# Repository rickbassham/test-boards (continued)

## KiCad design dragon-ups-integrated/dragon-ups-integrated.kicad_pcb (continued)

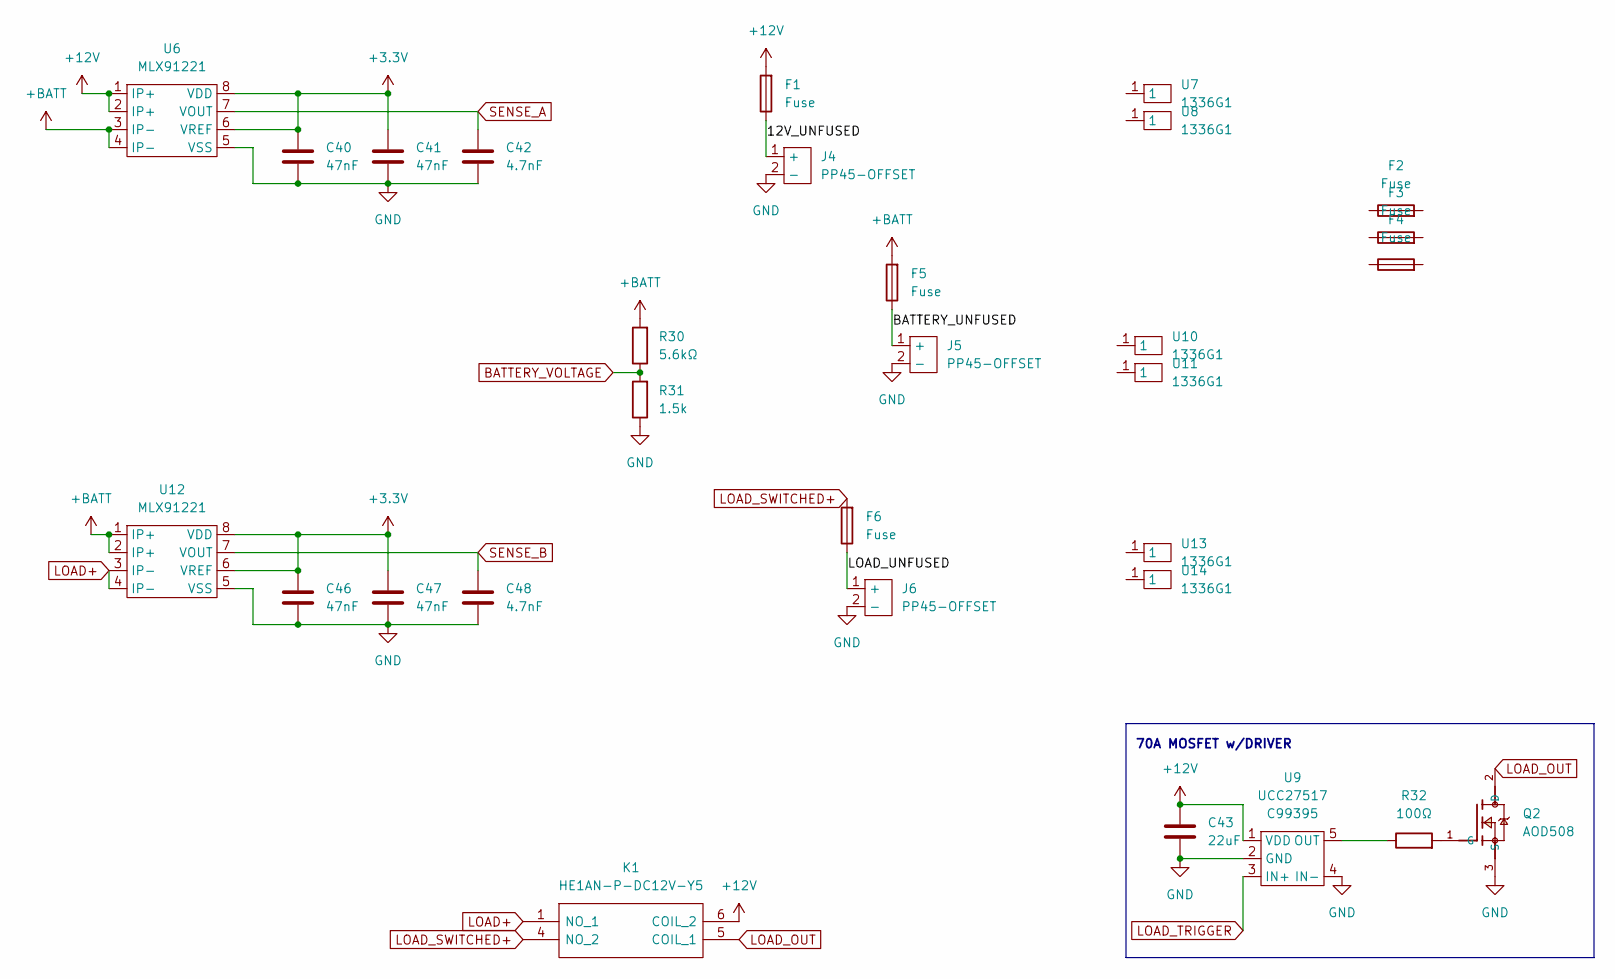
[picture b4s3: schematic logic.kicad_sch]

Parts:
C40, C41, C46, C47: 47nF; C_0603_1608Metric; LCSC C1622
C42, C48: 4.7nF; C_0603_1608Metric; LCSC C53987
C43: 22uF; C_0805_2012Metric; LCSC C45783
F1, F5, F6: Fuse; Keystone 3522-2 Fuse Holder; Manufacturer Part 3522-2; DigiKey Part 36-3522-2-ND
F2, F3, F4: Fuse; Manufacturer Part 0287030.PXCN; DigiKey Part F4202-ND
J4, J5, J6: PP45-OFFSET; PP45-SHORT; Manufacturer Part 1336G1; DigiKey Part 2243-1336G1-ND
K1: HE1AN-P-DC12V-Y5; HE1ANPDC6VY5; Manufacturer_Part_Number HE1AN-P-DC6V-Y5; Mouser Part Number 769-HE1AN-P-DC6V-Y5
Q2: AOD508; TO-252-2; LCSC C80964
R30: 5.6kΩ; R_0805_2012Metric; LCSC C4382
R31: 1.5k; R_0805_2012Metric; LCSC C4310
R32: 100Ω; R_0603_1608Metric; LCSC C22775
U6, U12: MLX91221; SOIC-8_3.9x4.9mm_P1.27mm
U7, U8, U10, U11, U13, U14: 1336G1; Manufacturer Part 1336G1; DigiKey Part 2243-1336G1-ND
U9: UCC27517; SOT-23-5; LCSC C99395

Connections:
+3V3: C40.1, C41.1, C46.1, C47.1, U6.6 (VREF), U6.8 (VDD), U12.6 (VREF), U12.8 (VDD); also elsewhere on the board
+12V: C43.1, F1.2, K1.6 (COIL_2), U6.1 (IP+), U6.2 (IP+), U9.1 (VDD); also elsewhere on the board
+BATT: F5.2, R30.2, U6.3 (IP-), U6.4 (IP-), U12.1 (IP+), U12.2 (IP+)
/Logic/12V_UNFUSED: F1.1, J4.1 (+)
/Logic/BATTERY_UNFUSED: F5.1, J5.1 (+)
/Logic/LOAD_UNFUSED: F6.1, J6.1 (+)
BATTERY_VOLTAGE: R30.1, R31.2; also elsewhere on the board
GND: C40.2, C41.2, C42.2, C43.2, C46.2, C47.2, C48.2, J4.2 (-), J5.2 (-), J6.2 (-), Q2.3 (S), R31.1, U6.5 (VSS), U9.2 (GND), U9.4 (IN-), U12.5 (VSS); also elsewhere on the board
LOAD+: K1.1 (NO_1), U12.3 (IP-), U12.4 (IP-)
LOAD_OUT: K1.5 (COIL_1), Q2.2 (D)
LOAD_SWITCHED+: F6.2, K1.4 (NO_2)
LOAD_TRIGGER: U9.3 (IN+)
unnamed: Q2.1 (G), R32.2
unnamed: R32.1, U9.5 (OUT)
SENSE_A: C42.1, U6.7 (VOUT); also elsewhere on the board
SENSE_B: C48.1, U12.7 (VOUT); also elsewhere on the board

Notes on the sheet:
70A MOSFET w/DRIVER

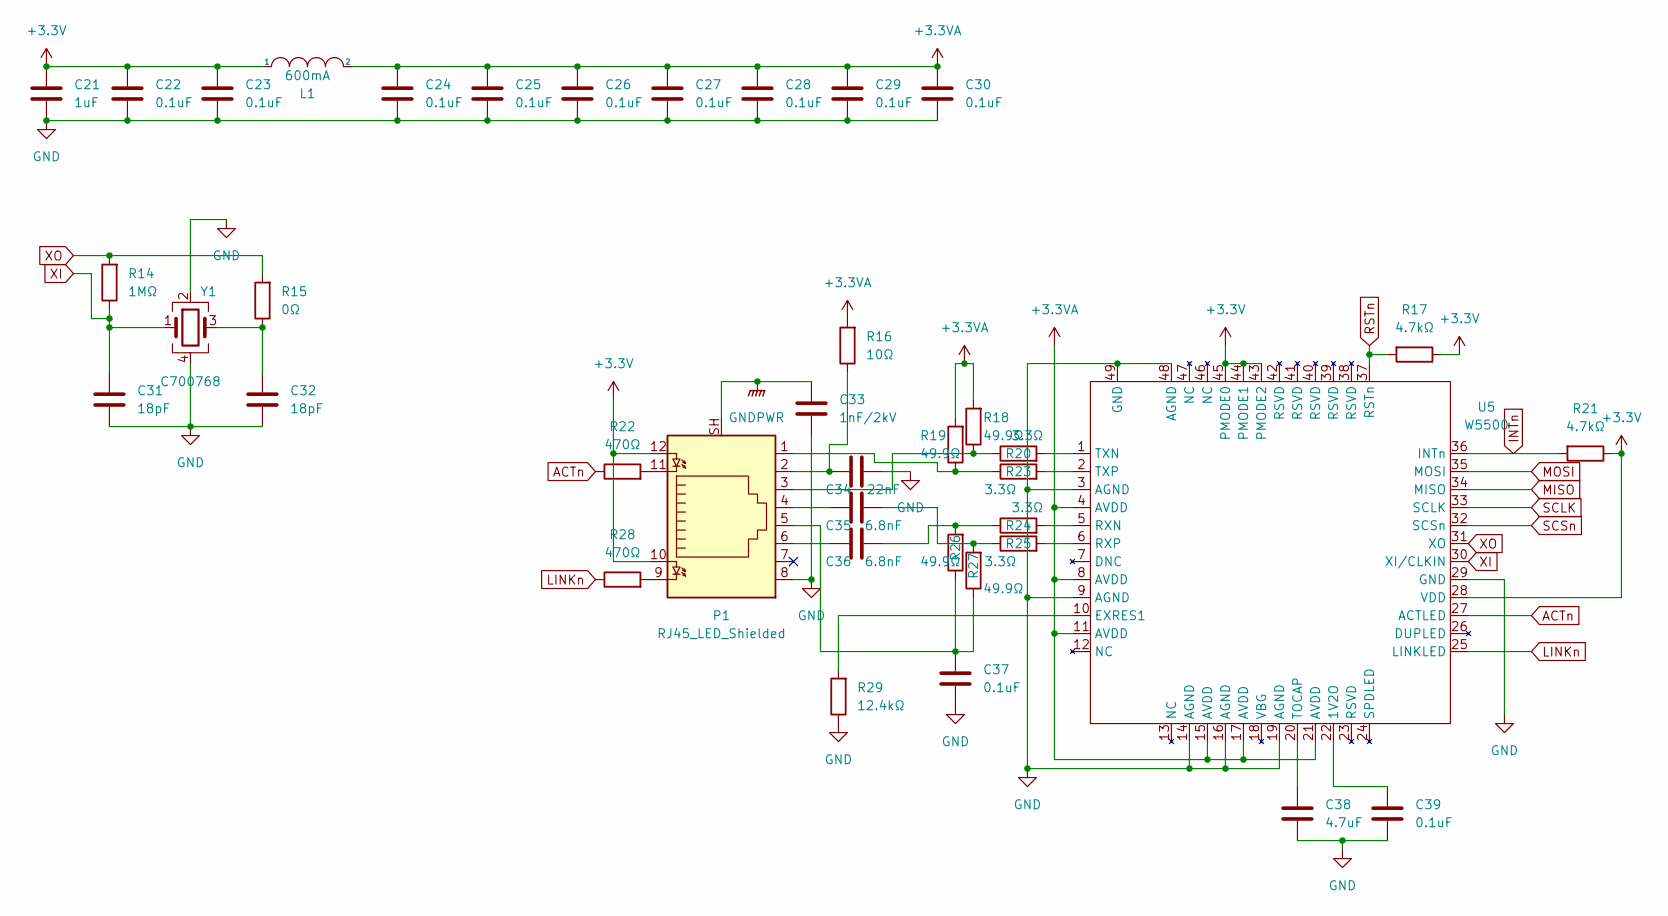
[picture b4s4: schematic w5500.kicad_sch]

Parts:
C21: 1uF; C_0402_1005Metric; LCSC C52923
C22, C23, C24, C25, C26, C27, C28, C29, C30, C37, C39: 0.1uF; C_0402_1005Metric; LCSC C1525
C31, C32: 18pF; C_0402_1005Metric; LCSC C1549
C33: 1nF/2kV; C_1206_3216Metric; LCSC C9196
C34: 22nF; C_0402_1005Metric; LCSC C1532
C35, C36: 6.8nF; C_0402_1005Metric; LCSC C1542
C38: 4.7uF; C_0402_1005Metric; LCSC C23733
L1: 600mA; L_0603_1608Metric; LCSC C280478
P1: RJ45_LED_Shielded; J1B1211CCD; Manufacturer PN J1B1211CCD; LCSC C910371
R14: 1MΩ; R_0402_1005Metric; LCSC C26083
R15: 0Ω; R_0402_1005Metric; LCSC C17168
R16: 10Ω; R_0402_1005Metric; LCSC C25077
R17, R21: 4.7kΩ; R_0402_1005Metric; LCSC C25900
R18, R19, R26, R27: 49.9Ω; R_0402_1005Metric; LCSC C25120
R20, R23, R24, R25: 3.3Ω; R_0402_1005Metric; LCSC C269403
R22, R28: 470Ω; R_0402_1005Metric; LCSC C25117
R29: 12.4kΩ; R_0402_1005Metric; LCSC C11692
U5: W5500; LQFP-48-1EP_7x7mm_P0.5mm_EP3.6x3.6mm; LCSC C32843
Y1: C700768; Crystal_SMD_3225-4Pin_3.2x2.5mm; LCSC C700768

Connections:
+3.3VA: C24.1, C25.1, C26.1, C27.1, C28.1, C29.1, C30.1, L1.2, R16.2, R18.2, R19.2, U5.4 (AVDD), U5.8 (AVDD), U5.11 (AVDD), U5.15 (AVDD), U5.17 (AVDD), U5.21 (AVDD)
+3V3: C21.1, C22.1, C23.1, L1.1, P1.10, P1.12, R17.1, R21.1, U5.28 (VDD), U5.43 (PMODE2), U5.44 (PMODE1), U5.45 (PMODE0); also elsewhere on the board
ACTn: R22.1, U5.27 (ACTLED)
GND: C21.2, C22.2, C23.2, C24.2, C25.2, C26.2, C27.2, C28.2, C29.2, C30.2, C31.2, C32.2, C33.2, C34.2, C37.2, C38.2, C39.2, P1.8, R29.1, U5.3 (AGND), U5.9 (AGND), U5.14 (AGND), U5.16 (AGND), U5.19 (AGND), U5.29 (GND), U5.48 (AGND), U5.49 (GND), Y1.2, Y1.4; also elsewhere on the board
GNDPWR: C33.1, P1.SH
INTn: R21.2, U5.36 (INTn); also elsewhere on the board
LINKn: R28.1, U5.25 (LINKLED)
MISO: U5.34 (MISO); also elsewhere on the board
MOSI: U5.35 (MOSI); also elsewhere on the board
unnamed: C32.1, R15.1, Y1.3
unnamed: C34.1, P1.2, R16.1
unnamed: C35.1, P1.4
unnamed: C35.2, R25.1, R27.2
unnamed: C36.1, P1.6
unnamed: C36.2, R24.1, R26.2
unnamed: C37.1, P1.5, R26.1, R27.1
unnamed: C38.1, U5.20 (TOCAP)
unnamed: C39.1, U5.22 (1V2O)
unnamed: P1.1, R19.1, R23.1
unnamed: P1.3, R18.1, R20.1
unnamed: P1.9, R28.2
unnamed: P1.11, R22.2
unnamed: R20.2, U5.1 (TXN)
unnamed: R23.2, U5.2 (TXP)
unnamed: R24.2, U5.5 (RXN)
unnamed: R25.2, U5.6 (RXP)
unnamed: R29.2, U5.10 (EXRES1)
RSTn: R17.2, U5.37 (RSTn); also elsewhere on the board
SCLK: U5.33 (SCLK); also elsewhere on the board
SCSn: U5.32 (SCSn); also elsewhere on the board
XI: C31.1, R14.1, U5.30 (XI/CLKIN), Y1.1
XO: R14.2, R15.2, U5.31 (XO)

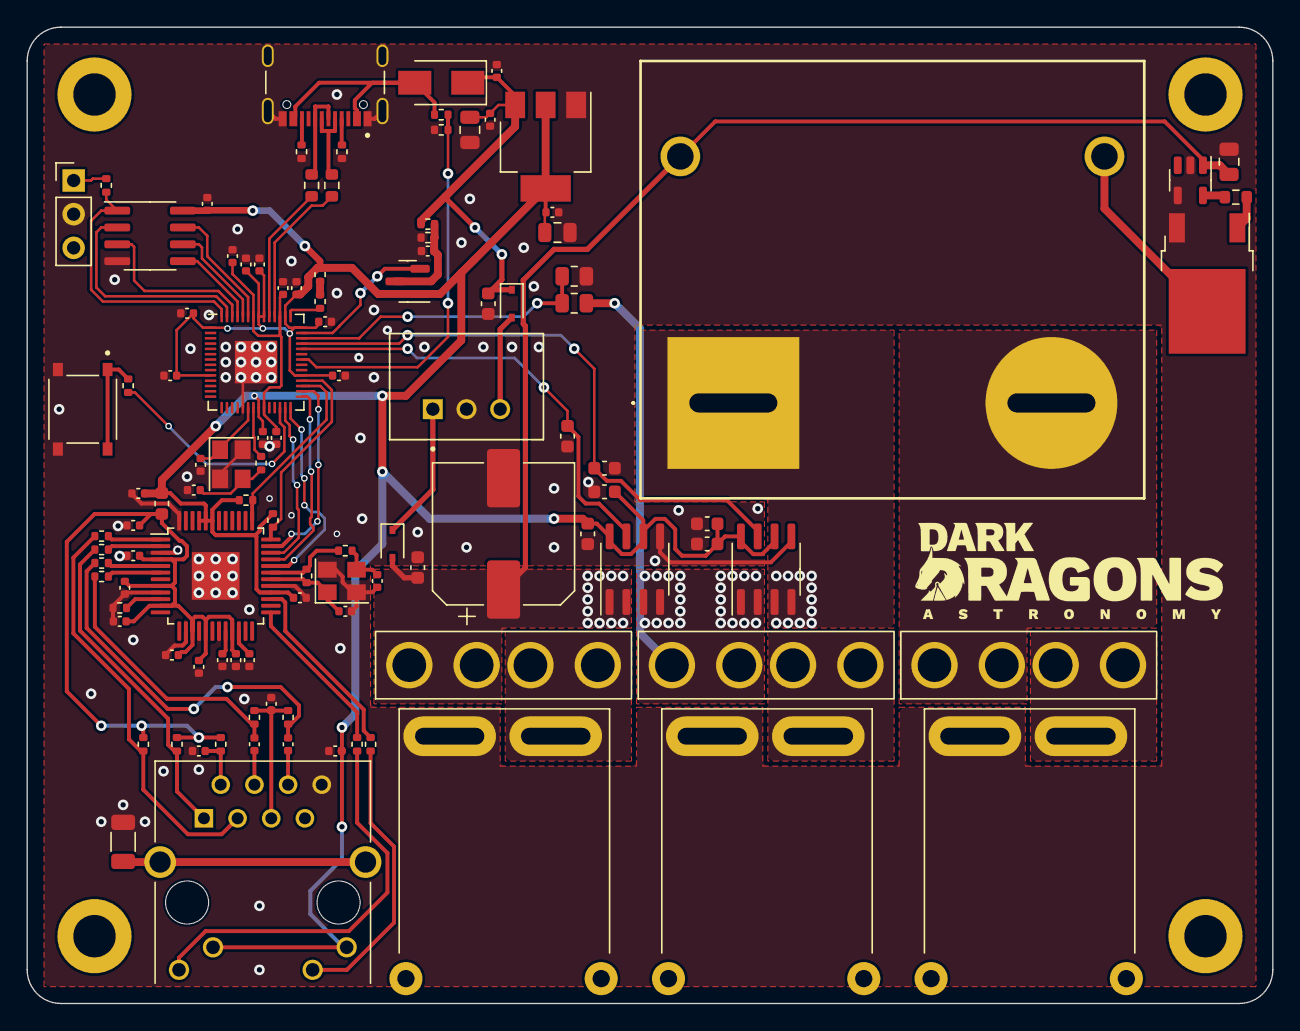
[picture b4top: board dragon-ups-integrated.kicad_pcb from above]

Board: 2 copper layers, 94.0 x 73.7 mm, 112 parts (0 on the bottom side), 73 nets.

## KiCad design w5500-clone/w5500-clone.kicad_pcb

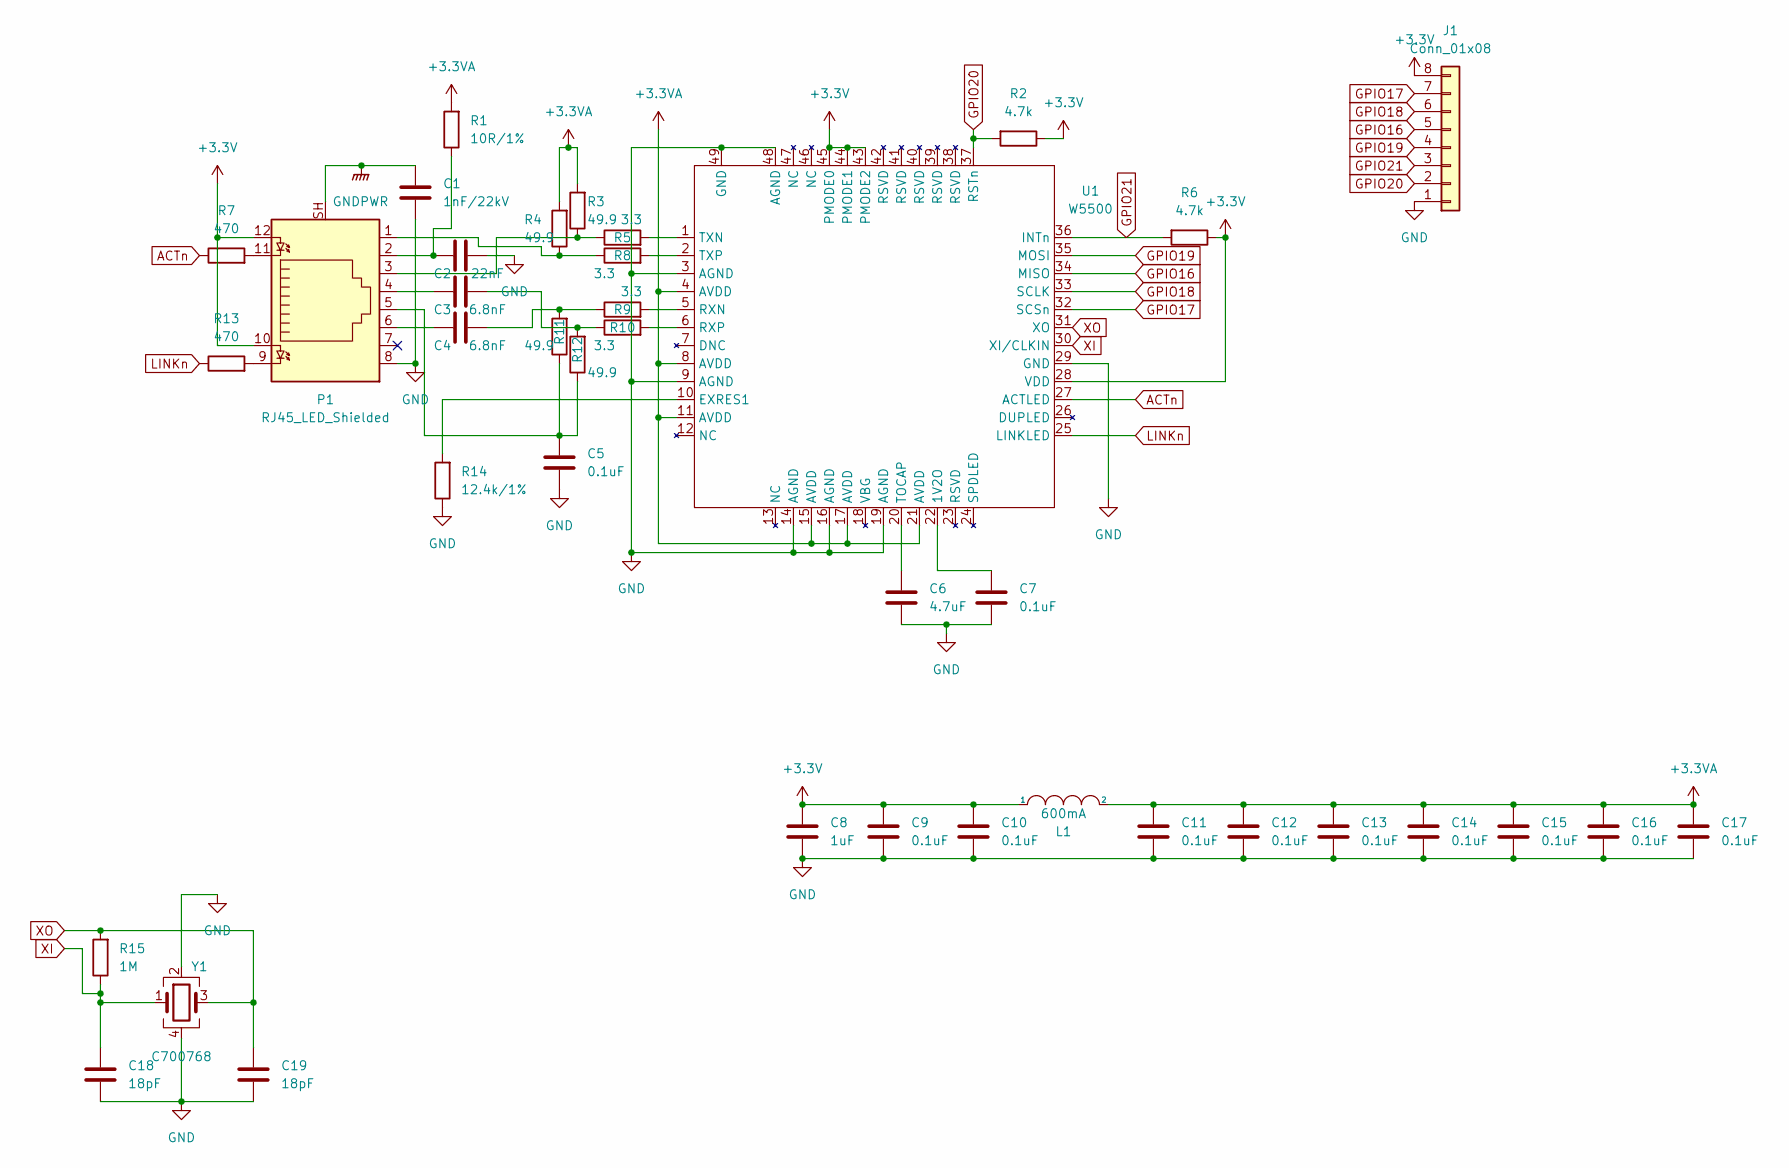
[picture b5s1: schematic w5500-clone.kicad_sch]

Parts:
C1: 1nF/22kV; C_1812_4532Metric; LCSC C304032
C2: 22nF; C_0402_1005Metric; LCSC C1532
C3, C4: 6.8nF; C_0402_1005Metric; LCSC C1542
C5, C7, C9, C10, C11, C12, C13, C14, C15, C16, C17: 0.1uF; C_0402_1005Metric; LCSC C1525
C6: 4.7uF; C_0402_1005Metric; LCSC C23733
C8: 1uF; C_0402_1005Metric; LCSC C52923
C18, C19: 18pF; C_0402_1005Metric; LCSC C1549
J1: Conn_01x08; PinHeader_1x08_P2.54mm_Vertical
L1: 600mA; L_0603_1608Metric; LCSC C280478
P1: RJ45_LED_Shielded; J1B1211CCD; Manufacturer PN J1B1211CCD; LCSC C910371
R1: 10R/1%; R_0402_1005Metric; LCSC C25077
R2, R6: 4.7k; R_0402_1005Metric; LCSC C25900
R3, R4, R11, R12: 49.9; R_0402_1005Metric; LCSC C25120
R5, R8, R9, R10: 3.3; R_0402_1005Metric; LCSC C270612
R7, R13: 470; R_0402_1005Metric; LCSC C25117
R14: 12.4k/1%; R_0402_1005Metric; LCSC C11692
R15: 1M; R_0402_1005Metric; LCSC C26083
U1: W5500; LQFP-48-1EP_7x7mm_P0.5mm_EP3.6x3.6mm; LCSC C32843
Y1: C700768; Crystal_SMD_3225-4Pin_3.2x2.5mm; LCSC C700768

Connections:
+3.3VA: C11.1, C12.1, C13.1, C14.1, C15.1, C16.1, C17.1, L1.2, R1.2, R3.2, R4.2, U1.4 (AVDD), U1.8 (AVDD), U1.11 (AVDD), U1.15 (AVDD), U1.17 (AVDD), U1.21 (AVDD)
+3V3: C8.1, C9.1, C10.1, J1.8, L1.1, P1.10, P1.12, R2.1, R6.1, U1.28 (VDD), U1.43 (PMODE2), U1.44 (PMODE1), U1.45 (PMODE0)
ACTn: R7.1, U1.27 (ACTLED)
GND: C1.2, C2.2, C5.2, C6.2, C7.2, C8.2, C9.2, C10.2, C11.2, C12.2, C13.2, C14.2, C15.2, C16.2, C17.2, C18.2, C19.2, J1.1, P1.8, R14.1, U1.3 (AGND), U1.9 (AGND), U1.14 (AGND), U1.16 (AGND), U1.19 (AGND), U1.29 (GND), U1.48 (AGND), U1.49 (GND), Y1.2, Y1.4
GNDPWR: C1.1, P1.SH
GPIO16: J1.5, U1.34 (MISO)
GPIO17: J1.7, U1.32 (SCSn)
GPIO18: J1.6, U1.33 (SCLK)
GPIO19: J1.4, U1.35 (MOSI)
GPIO20: J1.2, R2.2, U1.37 (RSTn)
GPIO21: J1.3, R6.2, U1.36 (INTn)
LINKn: R13.1, U1.25 (LINKLED)
unnamed: C2.1, P1.2, R1.1
unnamed: C3.1, P1.4
unnamed: C3.2, R10.1, R12.2
unnamed: C4.1, P1.6
unnamed: C4.2, R9.1, R11.2
unnamed: C5.1, P1.5, R11.1, R12.1
unnamed: C6.1, U1.20 (TOCAP)
unnamed: C7.1, U1.22 (1V2O)
unnamed: P1.1, R4.1, R8.1
unnamed: P1.3, R3.1, R5.1
unnamed: P1.9, R13.2
unnamed: P1.11, R7.2
unnamed: R5.2, U1.1 (TXN)
unnamed: R8.2, U1.2 (TXP)
unnamed: R9.2, U1.5 (RXN)
unnamed: R10.2, U1.6 (RXP)
unnamed: R14.2, U1.10 (EXRES1)
XI: C18.1, R15.1, U1.30 (XI/CLKIN), Y1.1
XO: C19.1, R15.2, U1.31 (XO), Y1.3

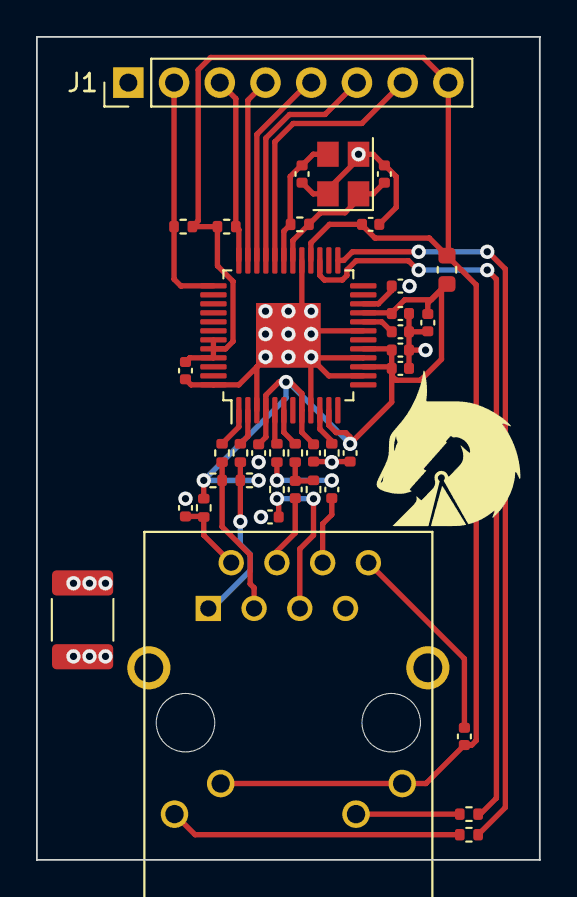
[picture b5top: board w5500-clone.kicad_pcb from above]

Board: 2 copper layers, 27.9 x 45.7 mm, 39 parts (0 on the bottom side), 31 nets.

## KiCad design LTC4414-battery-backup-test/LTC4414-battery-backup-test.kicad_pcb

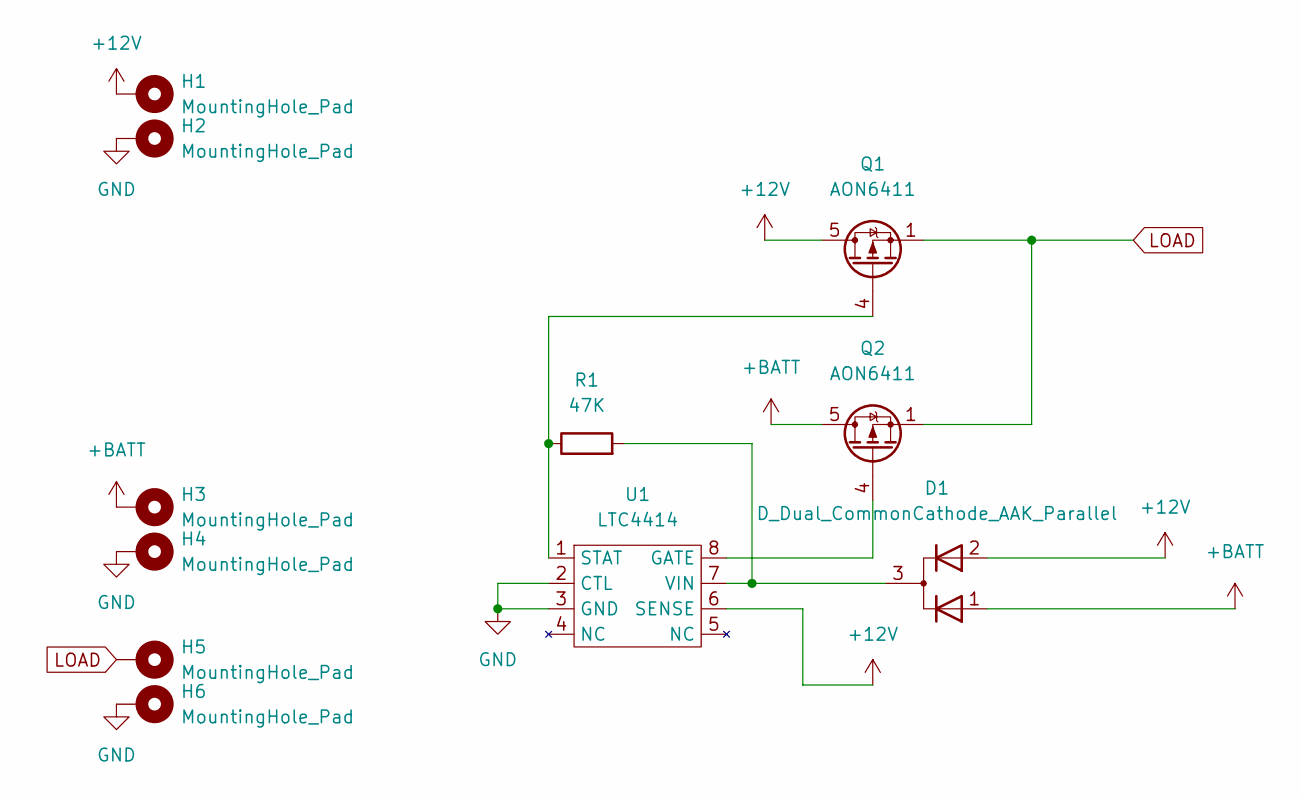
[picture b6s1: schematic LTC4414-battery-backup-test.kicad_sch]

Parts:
D1: D_Dual_CommonCathode_AAK_Parallel; SOT-23; LCSC C2894716
H1, H2, H3, H4, H5, H6: MountingHole_Pad; MountingHole_3.2mm_M3_DIN965_Pad
Q1, Q2: AON6411; AO_DFN-8-1EP_5.55x5.2mm_P1.27mm_EP4.12x4.6mm; LCSC C81007
R1: 47K; R_0402_1005Metric; LCSC C144757
U1: LTC4414; MSOP-8_3x3mm_P0.65mm; LCSC C580900

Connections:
+12V: D1.2 (K), H1.1, Q1.5 (D), U1.6 (SENSE)
+BATT: D1.1 (K), H3.1, Q2.5 (D)
GND: H2.1, H4.1, H6.1, U1.2 (CTL), U1.3 (GND)
LOAD: H5.1, Q1.1 (S), Q1.2 (S), Q1.3 (S), Q2.1 (S), Q2.2 (S), Q2.3 (S)
unnamed: D1.3 (A), R1.2, U1.7 (VIN)
unnamed: Q1.4 (G), R1.1, U1.1 (STAT)
unnamed: Q2.4 (G), U1.8 (GATE)

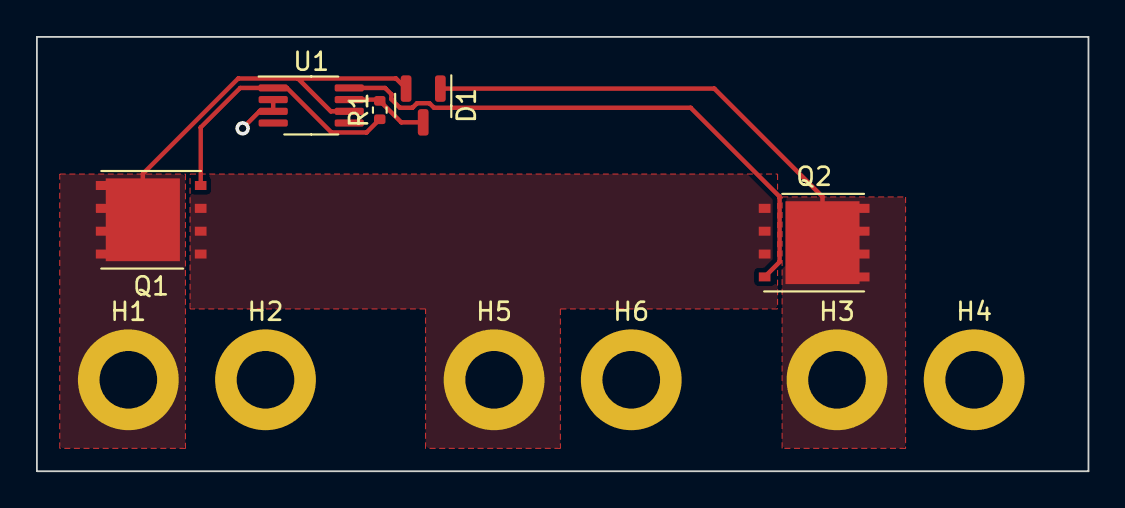
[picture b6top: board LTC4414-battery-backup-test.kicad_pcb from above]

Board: 2 copper layers, 58.4 x 24.1 mm, 11 parts (0 on the bottom side), 7 nets.

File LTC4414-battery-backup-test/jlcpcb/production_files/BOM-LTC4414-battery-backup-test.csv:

Comment,Designator,Footprint,LCSC
47K,R1,R_0402_1005Metric,C144757
D_Dual_CommonCathode_AAK_Parallel,D1,SOT-23,C2894716
LTC4414,U1,MSOP-8_3x3mm_P0.65mm,C580900
AON6411,"Q1,Q2",AO_DFN-8-1EP_5.55x5.2mm_P1.27mm_EP4.12x4.6mm,C81007

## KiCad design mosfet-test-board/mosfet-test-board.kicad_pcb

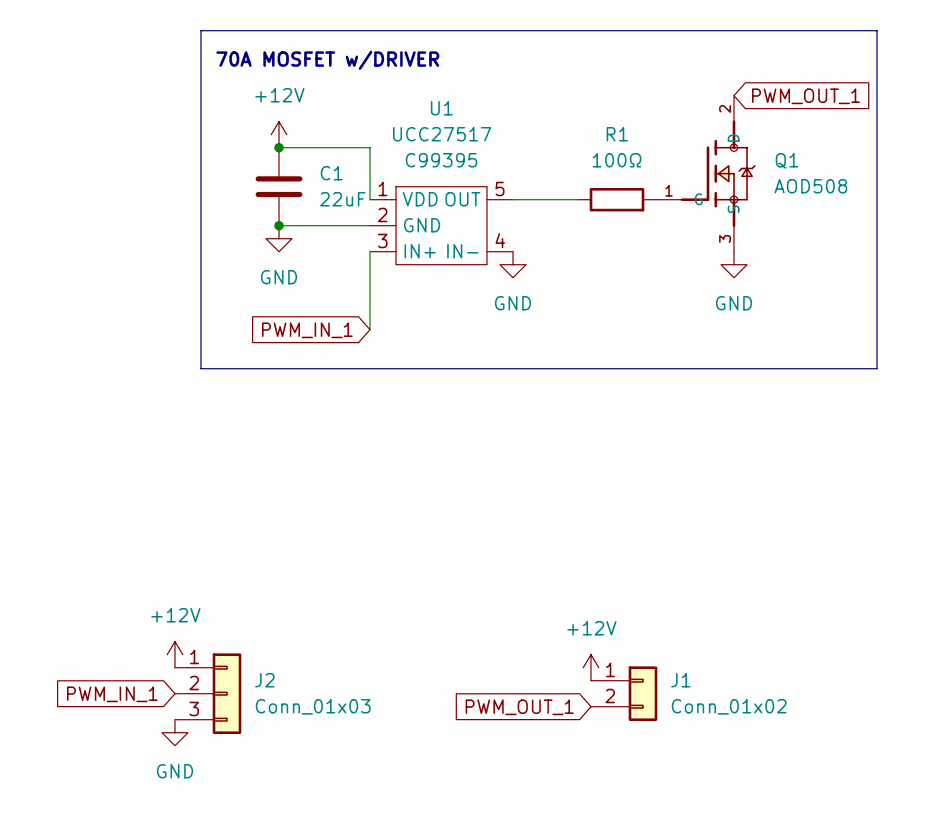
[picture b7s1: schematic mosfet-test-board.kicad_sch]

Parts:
C1: 22uF; C_0603_1608Metric; LCSC C268016
J1: Conn_01x02; PinHeader_1x02_P2.54mm_Vertical
J2: Conn_01x03; PinHeader_1x03_P2.54mm_Vertical
Q1: AOD508; TO-252-2; LCSC C80964
R1: 100Ω; R_0603_1608Metric; LCSC C105588
U1: UCC27517; SOT-23-5; LCSC C99395

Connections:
+12V: C1.1, J1.1, J2.1, U1.1 (VDD)
GND: C1.2, J2.3, Q1.3 (S), U1.2 (GND), U1.4 (IN-)
unnamed: Q1.1 (G), R1.2
unnamed: R1.1, U1.5 (OUT)
PWM_IN_1: J2.2, U1.3 (IN+)
PWM_OUT_1: J1.2, Q1.2 (D)

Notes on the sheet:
70A MOSFET w/DRIVER

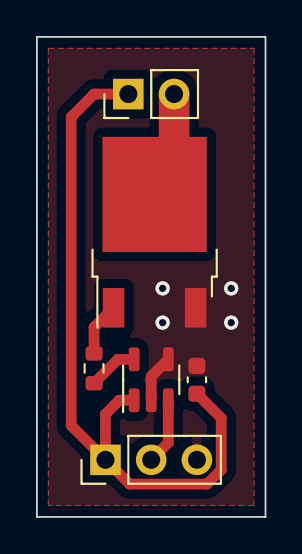
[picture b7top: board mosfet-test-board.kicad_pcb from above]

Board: 2 copper layers, 12.7 x 26.7 mm, 6 parts (0 on the bottom side), 6 nets.

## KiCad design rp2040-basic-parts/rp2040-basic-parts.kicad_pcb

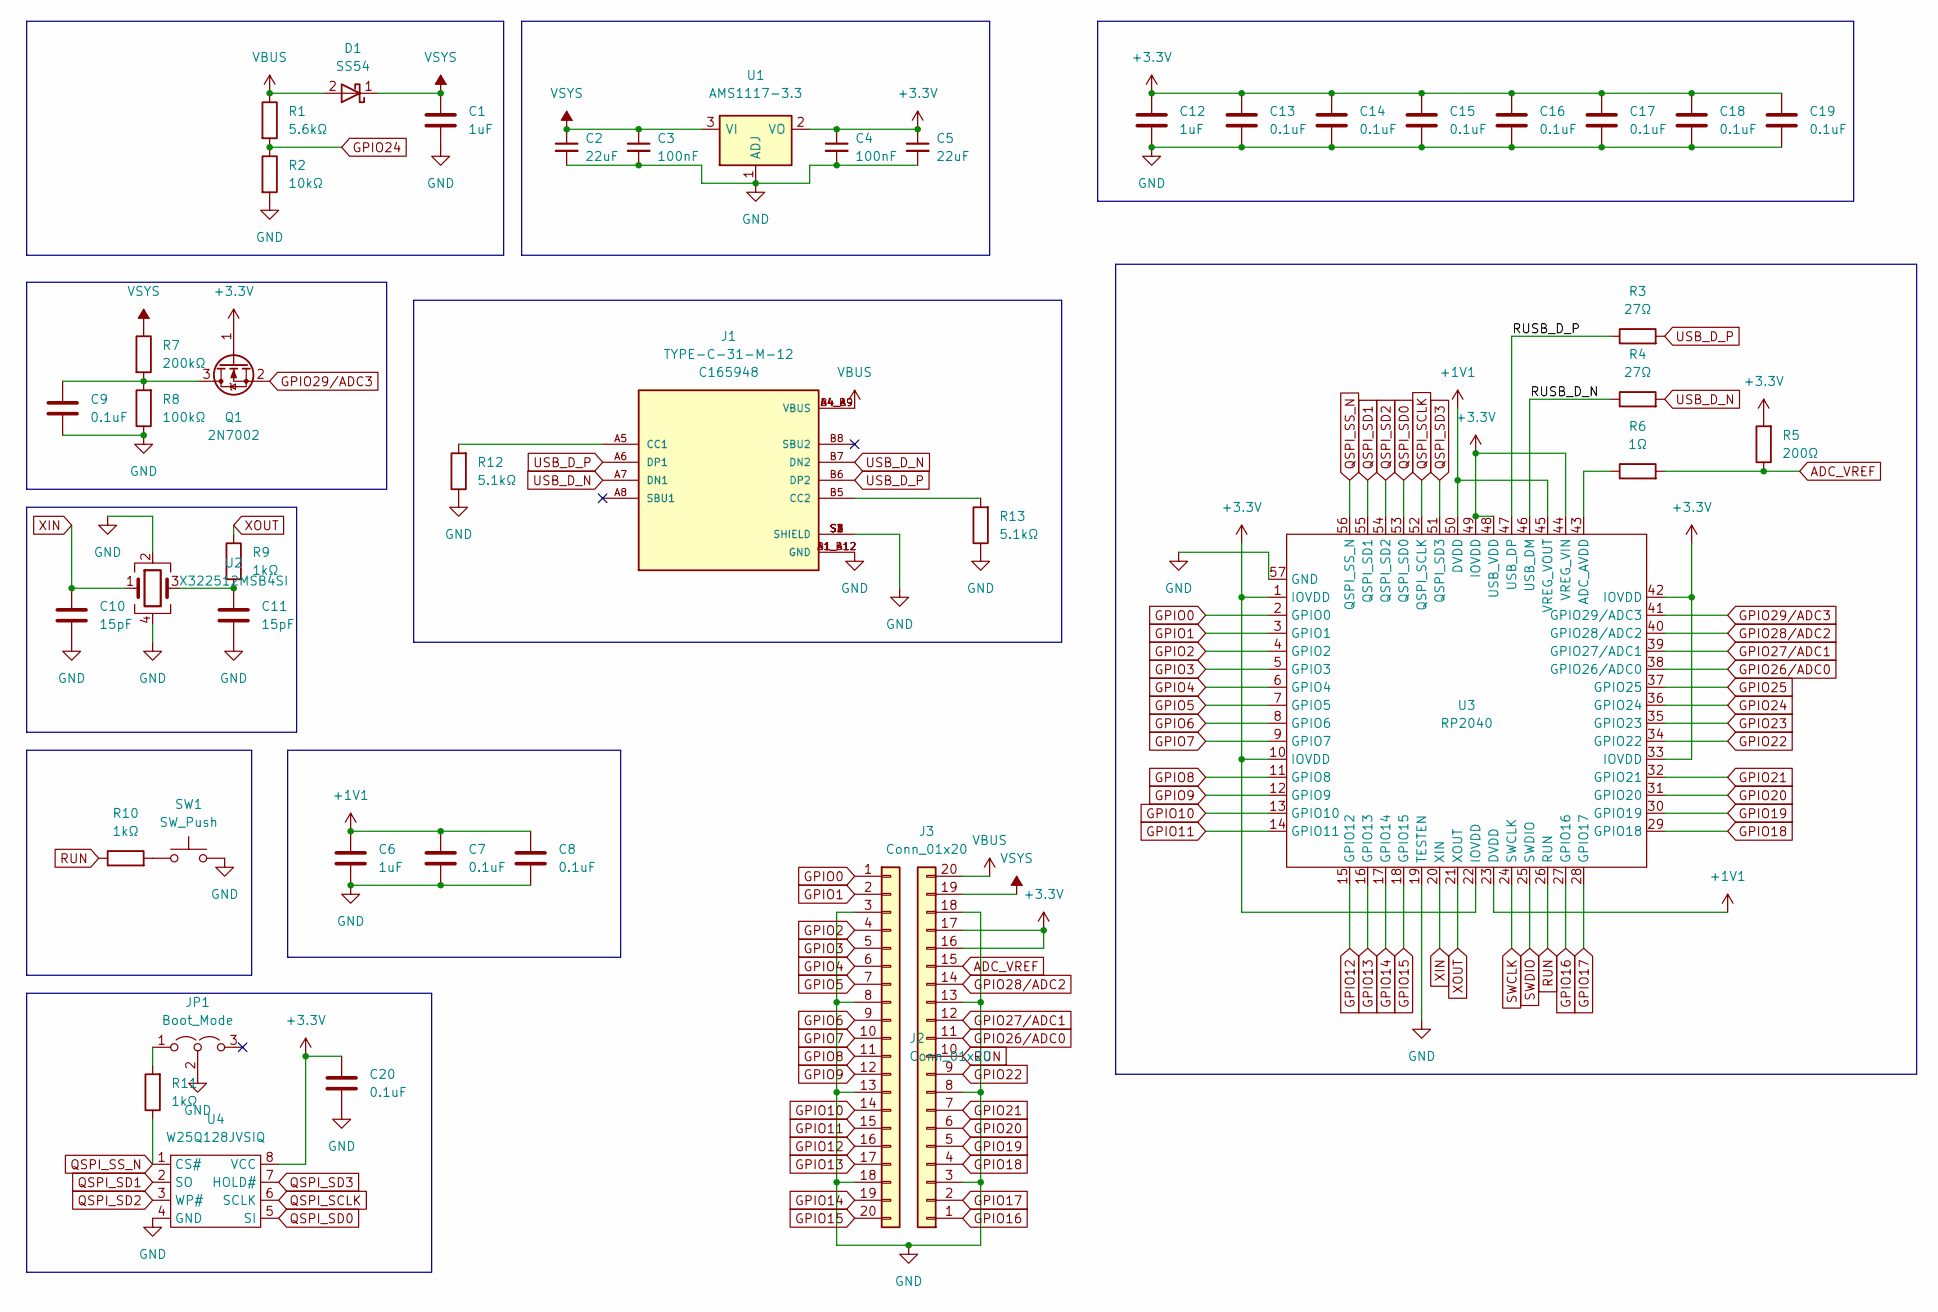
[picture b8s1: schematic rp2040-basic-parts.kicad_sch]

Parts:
C1, C6, C12: 1uF; C_0402_1005Metric; LCSC C52923
C2, C5: 22uF; C_0805_2012Metric; LCSC C45783
C3, C4: 100nF; C_0402_1005Metric; LCSC C307331
C7, C8, C9, C13, C14, C15, C16, C17, C18, C19, C20: 0.1uF; C_0402_1005Metric; LCSC C1525
C10, C11: 15pF; C_0402_1005Metric; LCSC C1548
D1: SS54; D_SMA; LCSC C22452
J1: TYPE-C-31-M-12; HRO_TYPE-C-31-M-12; LCSC C165948
J2, J3: Conn_01x20; PinHeader_1x20_P2.54mm_Vertical
JP1: Boot_Mode; PinHeader_1x03_P2.54mm_Vertical
Q1: 2N7002; SOT-23; LCSC C8545
R1: 5.6kΩ; R_0402_1005Metric; LCSC C25908
R2: 10kΩ; R_0402_1005Metric; LCSC C25744
R3, R4: 27Ω; R_0603_1608Metric; LCSC C25190
R5: 200Ω; R_0402_1005Metric; LCSC C25087
R6: 1Ω; R_0402_1005Metric; LCSC C25086
R7: 200kΩ; R_0402_1005Metric; LCSC C25764
R8: 100kΩ; R_0402_1005Metric; LCSC C25741
R9, R10, R11: 1kΩ; R_0402_1005Metric; LCSC C11702
R12, R13: 5.1kΩ; R_0402_1005Metric
SW1: SW_Push; SW_TS-1187A-B-A-B; LCSC C318884
U1: AMS1117-3.3; SOT-223-3_TabPin2; LCSC C6186
U2: X322512MSB4SI; Crystal_SMD_3225-4Pin_3.2x2.5mm; LCSC C9002
U3: RP2040; LCSC C2040
U4: W25Q128JVSIQ; SOIC-8_3.9x4.9mm_P1.27mm; LCSC C97521

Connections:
+1V1: C6.1, C7.1, C8.1, U3.23 (DVDD), U3.45 (VREG_VOUT), U3.50 (DVDD)
+3V3: C4.1, C5.1, C12.1, C13.1, C14.1, C15.1, C16.1, C17.1, C18.1, C19.1, C20.1, J3.16, J3.17, Q1.1 (G), R5.2, U1.2 (VO), U3.1 (IOVDD), U3.10 (IOVDD), U3.22 (IOVDD), U3.33 (IOVDD), U3.42 (IOVDD), U3.44 (VREG_VIN), U3.48 (USB_VDD), U3.49 (IOVDD), U4.8 (VCC)
/RUSB_D_N: R4.1, U3.46 (USB_DM)
/RUSB_D_P: R3.1, U3.47 (USB_DP)
ADC_VREF: J3.15, R5.1, R6.2
GND: C1.2, C2.2, C3.2, C4.2, C5.2, C6.2, C7.2, C8.2, C9.2, C10.2, C11.2, C12.2, C13.2, C14.2, C15.2, C16.2, C17.2, C18.2, C19.2, C20.2, J1.A1_B12 (GND), J1.B1_A12 (GND), J1.S1 (SHIELD), J1.S2 (SHIELD), J1.S3 (SHIELD), J1.S4 (SHIELD), J2.3, J2.8, J2.13, J2.18, J3.3, J3.8, J3.13, J3.18, JP1.2 (C), R2.2, R8.1, R12.1, R13.1, SW1.2, U1.1 (ADJ), U2.2, U2.4, U3.19 (TESTEN), U3.57 (GND), U4.4 (GND)
GPIO0: J2.1, U3.2 (GPIO0)
GPIO1: J2.2, U3.3 (GPIO1)
GPIO2: J2.4, U3.4 (GPIO2)
GPIO3: J2.5, U3.5 (GPIO3)
GPIO4: J2.6, U3.6 (GPIO4)
GPIO5: J2.7, U3.7 (GPIO5)
GPIO6: J2.9, U3.8 (GPIO6)
GPIO7: J2.10, U3.9 (GPIO7)
GPIO8: J2.11, U3.11 (GPIO8)
GPIO9: J2.12, U3.12 (GPIO9)
GPIO10: J2.14, U3.13 (GPIO10)
GPIO11: J2.15, U3.14 (GPIO11)
GPIO12: J2.16, U3.15 (GPIO12)
GPIO13: J2.17, U3.16 (GPIO13)
GPIO14: J2.19, U3.17 (GPIO14)
GPIO15: J2.20, U3.18 (GPIO15)
GPIO16: J3.1, U3.27 (GPIO16)
GPIO17: J3.2, U3.28 (GPIO17)
GPIO18: J3.4, U3.29 (GPIO18)
GPIO19: J3.5, U3.30 (GPIO19)
GPIO20: J3.6, U3.31 (GPIO20)
GPIO21: J3.7, U3.32 (GPIO21)
GPIO22: J3.9, U3.34 (GPIO22)
GPIO23: U3.35 (GPIO23)
GPIO24: R1.2, R2.1, U3.36 (GPIO24)
GPIO25: U3.37 (GPIO25)
GPIO26/ADC0: J3.11, U3.38 (GPIO26/ADC0)
GPIO27/ADC1: J3.12, U3.39 (GPIO27/ADC1)
GPIO28/ADC2: J3.14, U3.40 (GPIO28/ADC2)
GPIO29/ADC3: Q1.2 (S), U3.41 (GPIO29/ADC3)
unnamed: C9.1, Q1.3 (D), R7.2, R8.2
unnamed: C11.1, R9.2, U2.3
unnamed: J1.A5 (CC1), R12.2
unnamed: J1.B5 (CC2), R13.2
unnamed: JP1.1 (A), R11.2
unnamed: R6.1, U3.43 (ADC_AVDD)
unnamed: R10.2, SW1.1
QSPI_SCLK: U3.52 (QSPI_SCLK), U4.6 (SCLK)
QSPI_SD0: U3.53 (QSPI_SD0), U4.5 (SI)
QSPI_SD1: U3.55 (QSPI_SD1), U4.2 (SO)
QSPI_SD2: U3.54 (QSPI_SD2), U4.3 (WP#)
QSPI_SD3: U3.51 (QSPI_SD3), U4.7 (HOLD#)
QSPI_SS_N: R11.1, U3.56 (QSPI_SS_N), U4.1 (CS#)
RUN: J3.10, R10.1, U3.26 (RUN)
SWCLK: U3.24 (SWCLK)
SWDIO: U3.25 (SWDIO)
USB_D_N: J1.A7 (DN1), J1.B7 (DN2), R4.2
USB_D_P: J1.A6 (DP1), J1.B6 (DP2), R3.2
VBUS: D1.2 (A), J1.A4_B9 (VBUS), J1.B4_A9 (VBUS), J3.20, R1.1
VSYS: C1.1, C2.1, C3.1, D1.1 (K), J3.19, R7.1, U1.3 (VI)
XIN: C10.1, U2.1, U3.20 (XIN)
XOUT: R9.1, U3.21 (XOUT)

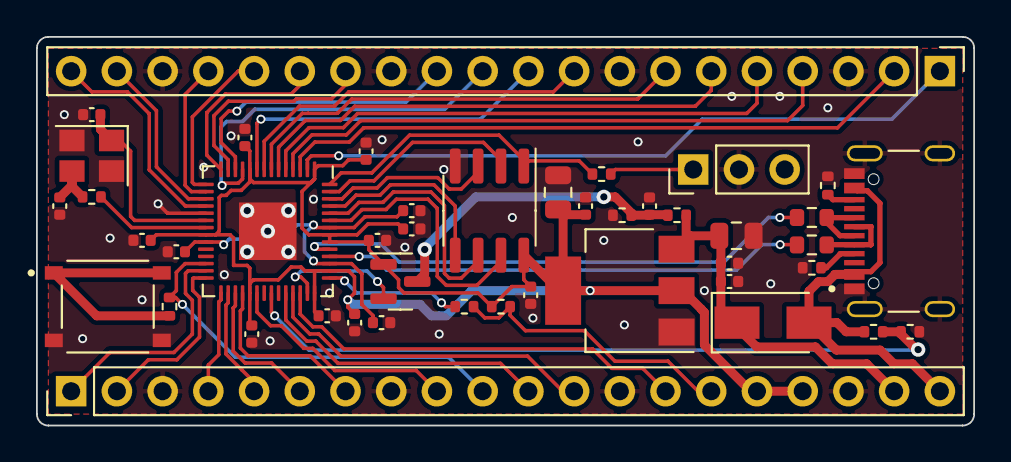
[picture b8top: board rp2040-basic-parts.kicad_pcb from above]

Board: 2 copper layers, 52.1 x 21.6 mm, 44 parts (0 on the bottom side), 54 nets.

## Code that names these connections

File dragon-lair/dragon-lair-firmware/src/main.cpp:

#define BUZZER_PIN 2
#define FOREWARD_MOTOR_PIN 4
#define BACKWARD_MOTOR_PIN 5
#define ON_PIN 6
#define OPEN_PIN 7
#define TOGGLE_CLOSE_PIN 8
#define ABORT_PIN 9
#define TOGGLE_OPEN_PIN 10
#define CLOSE_PIN 11
#define CLOSE_LIMIT_PIN 12
#define OPEN_LIMIT_PIN 13
#define SAFE_TO_MOVE_1_PIN 14
#define SAFE_TO_MOVE_2_PIN 15
#define AD_IO_PIN 26
#define MAX_SPEED_PIN 28

#include <Arduino.h>



void blinkErrorCode(int blinks)
{
    while (true)
    {
        for (int i = 0; i < blinks; i++)
        {
            digitalWrite(LED_BUILTIN, HIGH);
            sleep_ms(200);
            digitalWrite(LED_BUILTIN, LOW);
            sleep_ms(200);
        }

        sleep_ms(5000);
    }
}

void setup()
{
    sleep_ms(5000);

    analogReadResolution(8);

    analogWriteResolution(8);
    analogWriteFreq(5000);

    pinMode(LED_BUILTIN, OUTPUT);
    digitalWrite(LED_BUILTIN, LOW);

    pinMode(BUZZER_PIN, OUTPUT);
    digitalWrite(BUZZER_PIN, LOW);

    pinMode(FOREWARD_MOTOR_PIN, OUTPUT);
    analogWrite(FOREWARD_MOTOR_PIN, 0);

    pinMode(BACKWARD_MOTOR_PIN, OUTPUT);
    digitalWrite(BACKWARD_MOTOR_PIN, LOW);

    pinMode(ON_PIN, OUTPUT);
    digitalWrite(ON_PIN, LOW);

    pinMode(MAX_SPEED_PIN, INPUT);

    Serial.begin(9600);
}

bool forward = true;

void loop()
{
    int pin = forward ? FOREWARD_MOTOR_PIN : BACKWARD_MOTOR_PIN;

    digitalWrite(BACKWARD_MOTOR_PIN, LOW);
    digitalWrite(FOREWARD_MOTOR_PIN, LOW);

    Serial.println("Forward: " + String(forward));

    forward = !forward;

    digitalWrite(ON_PIN, HIGH);


    unsigned long start = millis();

    while (millis() - start < 5000)
    {
        analogWrite(LED_BUILTIN, 255);
        analogWrite(pin, 255);
        Serial.println(255);

        sleep_ms(100);
    }

    digitalWrite(ON_PIN, LOW);
    sleep_ms(2000);
}

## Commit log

2023-02-06 init
